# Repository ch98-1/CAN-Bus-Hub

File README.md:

# CAN Bus Hub

WARNING: Hub/Star topology is NOT recommended for a CAN bus. Use with heavy caution. Don't use if you don't know exactly what you are doing. It is heavily recommended to use the [CAN Bus Organizer](https://github.com/ch98-1/CAN-Bus-Organizer) instead.

Hub for a CAN bus. Add 1/4W 120 ohm axial resistor (6.5mm) or wires (~2mm diameter) as needed to the edge of the board. Use 2 holes next to the solder pad as strain relief if adding. Secure board with M4 screw. Make sure any unterminated stub is less than 30cm long.

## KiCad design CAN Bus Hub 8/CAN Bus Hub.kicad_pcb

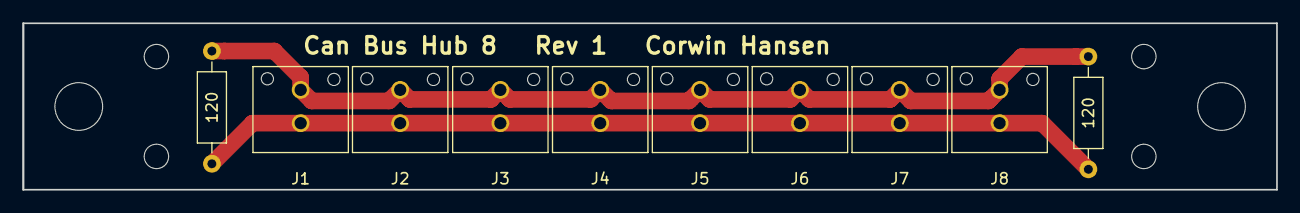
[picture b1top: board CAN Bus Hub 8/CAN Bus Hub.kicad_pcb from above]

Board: 2 copper layers, 113.0 x 15.0 mm, 16 parts (0 on the bottom side), 2 nets.

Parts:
J1, J2, J3, J4, J5, J6, J7, J8: Conn_01x02; Molex_Microfit3_Header_02x01_Straight_43045-0228
MK1, MK2: Mounting_Hole; MountingHole_4.3mm_M4
MK3, MK4, MK5, MK6: Strain_Relief; MountingHole_2.2mm_M2
R1, R2: 120; R_Axial_DIN0207_L6.3mm_D2.5mm_P10.16mm_Horizontal

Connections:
unnamed: J1.1, J2.1, J3.1, J4.1, J5.1, J6.1, J7.1, J8.1, R1.2, R2.2
unnamed: J1.2, J2.2, J3.2, J4.2, J5.2, J6.2, J7.2, J8.2, R1.1, R2.1

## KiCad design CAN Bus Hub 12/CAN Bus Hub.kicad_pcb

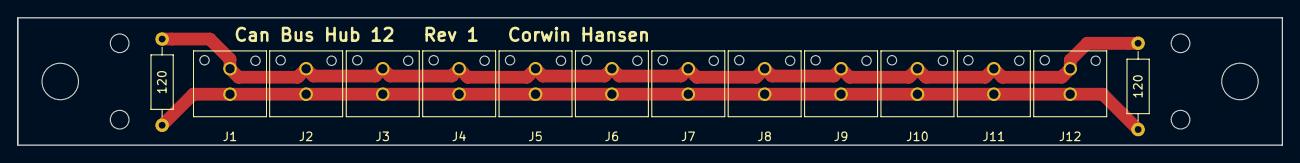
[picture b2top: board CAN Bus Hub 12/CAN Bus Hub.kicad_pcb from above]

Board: 2 copper layers, 149.0 x 15.0 mm, 20 parts (0 on the bottom side), 2 nets.

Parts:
J1, J2, J3, J4, J5, J6, J7, J8, J9, J10, J11, J12: Conn_01x02; Molex_Microfit3_Header_02x01_Straight_43045-0228
MK1, MK2: Mounting_Hole; MountingHole_4.3mm_M4
MK3, MK4, MK5, MK6: Strain_Relief; MountingHole_2.2mm_M2
R1, R2: 120; R_Axial_DIN0207_L6.3mm_D2.5mm_P10.16mm_Horizontal

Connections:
unnamed: J1.1, J2.1, J3.1, J4.1, J5.1, J6.1, J7.1, J8.1, J9.1, J10.1, J11.1, J12.1, R1.2, R2.2
unnamed: J1.2, J2.2, J3.2, J4.2, J5.2, J6.2, J7.2, J8.2, J9.2, J10.2, J11.2, J12.2, R1.1, R2.1

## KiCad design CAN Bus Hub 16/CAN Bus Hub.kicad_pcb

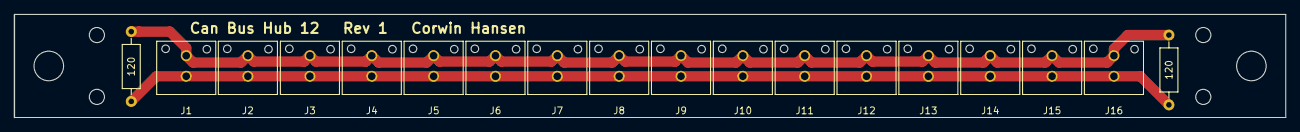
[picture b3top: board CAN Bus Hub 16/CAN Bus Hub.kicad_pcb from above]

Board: 2 copper layers, 185.0 x 15.0 mm, 24 parts (0 on the bottom side), 2 nets.

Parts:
J1, J2, J3, J4, J5, J6, J7, J8, J9, J10, J11, J12, J13, J14, J15, J16: Conn_01x02; Molex_Microfit3_Header_02x01_Straight_43045-0228
MK1, MK2: Mounting_Hole; MountingHole_4.3mm_M4
MK3, MK4, MK5, MK6: Strain_Relief; MountingHole_2.2mm_M2
R1, R2: 120; R_Axial_DIN0207_L6.3mm_D2.5mm_P10.16mm_Horizontal

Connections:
unnamed: J1.1, J2.1, J3.1, J4.1, J5.1, J6.1, J7.1, J8.1, J9.1, J10.1, J11.1, J12.1, J13.1, J14.1, J15.1, J16.1, R1.2, R2.2
unnamed: J1.2, J2.2, J3.2, J4.2, J5.2, J6.2, J7.2, J8.2, J9.2, J10.2, J11.2, J12.2, J13.2, J14.2, J15.2, J16.2, R1.1, R2.1

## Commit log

2018-02-11 Added Files for 16, 12, and 8 connector version
2018-02-11 Added Board Information
2018-02-16 Reduced solder mask clearance
2018-02-18 Added warning message and got cheaper part
2018-03-18 Updated Readme Warning
